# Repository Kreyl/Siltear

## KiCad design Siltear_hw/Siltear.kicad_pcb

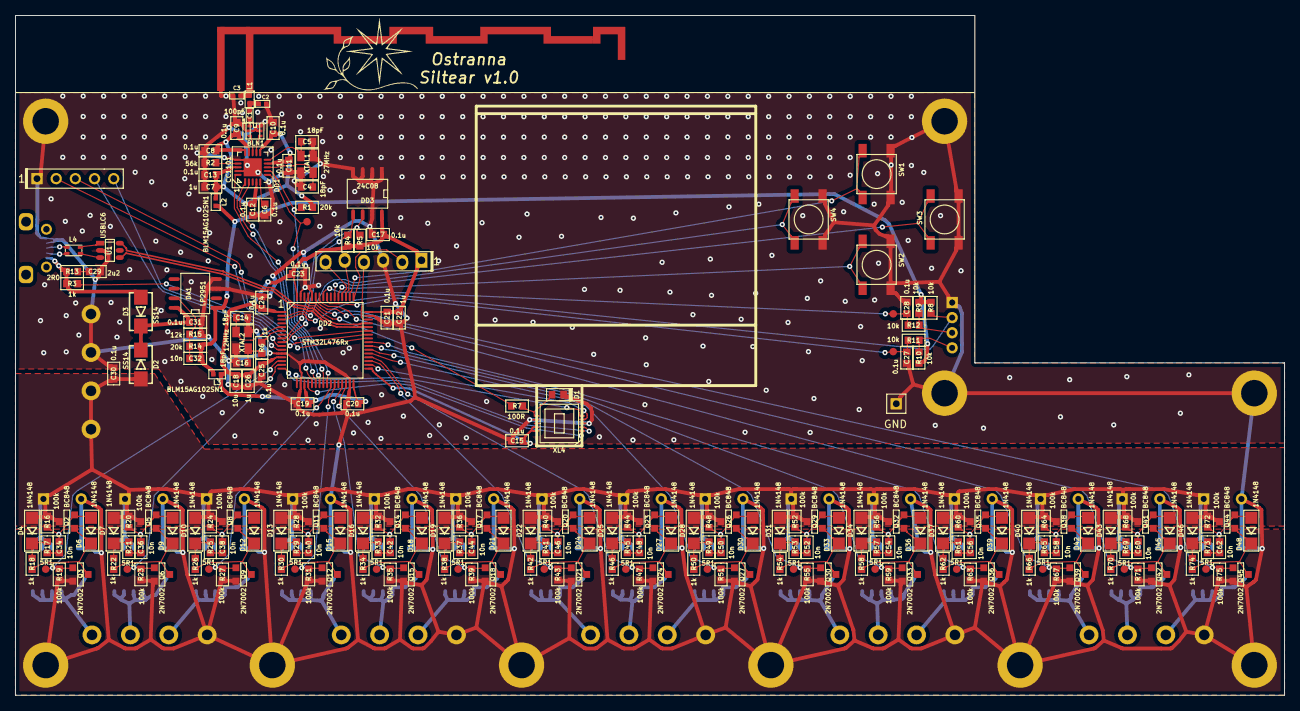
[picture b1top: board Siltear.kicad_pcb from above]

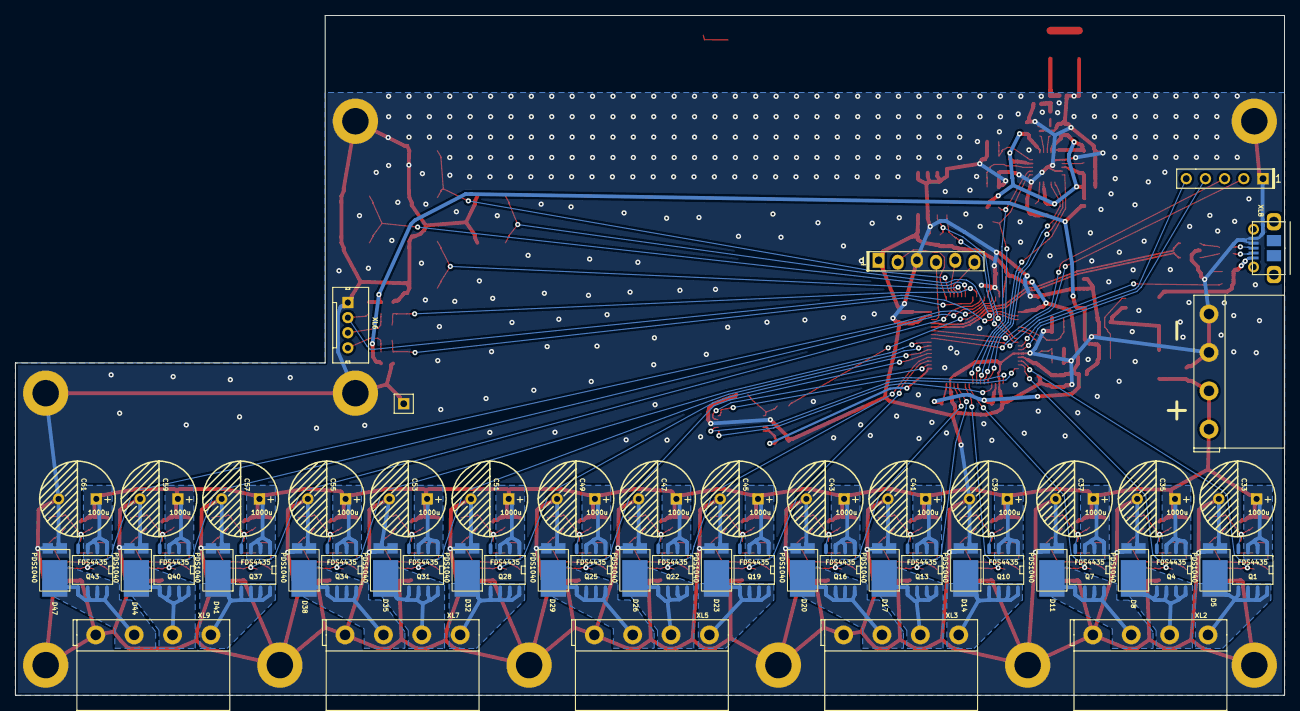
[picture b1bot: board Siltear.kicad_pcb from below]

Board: 4 copper layers, 168.0 x 90.0 mm, 288 parts (53 on the bottom side), 149 nets.

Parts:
ANT1: ANT_GENERAL; ANT_868_IFA_SIMPLEJOY
BLN1: BALUN868JOHANSON; BALUN_JOHANSON868
C1: 100pF; CAP_0402
C2, C3: ***; CAP_0402
C4, C5, C14, C16: 18pF; CAP_0603_Silks
C6, C8, C9, C10, C11, C12, C13, C15, C17, C19, C20, C21, C23, C24, C25, C27, C28, C30, C31: 0.1u; CAP_0603_Silks
C7, C22, C26: 1u; CAP_0603_Silks
C18: 10u; CAP_0603_Silks
C29: 2u2; CAP_0603_Silks
C32, C34, C36, C38, C40, C42, C44, C46, C48, C50, C52, C54, C56, C58, C60, C62: 10n; CAP_0603_Silks
C33, C35, C37, C39, C41, C43, C45, C47, C49, C51, C53, C55, C57, C59, C61: 1000u; CAP_10xxR
D1: LED; LED_0603
D2, D3: SS14; SMA_DO214AC
D4, D6, D7, D9, D10, D12, D13, D15, D16, D18, D19, D21, D22, D24, D25, D27, D28, D30, D31, D33, D34, D36, D37, D39, D40, D42, D43, D45, D46, D48: 1N4148; SOD80C
D5, D8, D11, D14, D17, D20, D23, D26, D29, D32, D35, D38, D41, D44, D47: PDS1040; PowerDI5
DA1: LP2951; SO8_150MIL
DD1: CC1101; QFN20
DD2: STM32L476Rx; LQFP64
DD3: 24C08; SO8_150MIL
HOLE1, HOLE2, HOLE3, HOLE4, HOLE5, HOLE6, HOLE7, HOLE8, HOLE9, HOLE10: HOLE_METALLED; Hole3_5_out6mm
L1: ***; IND_0402
L2, L3: BLM15AG102SN1; IND_0402
L4: 90R; DLW21SN
Logo1: Logo; Ostranna_12d7_10d1
Q1, Q4, Q7, Q10, Q13, Q16, Q19, Q22, Q25, Q28, Q31, Q34, Q37, Q40, Q43: FDS4435; SO8_150MIL
Q2, Q5, Q8, Q11, Q14, Q17, Q20, Q23, Q26, Q29, Q32, Q35, Q38, Q41, Q44: BC848; SOT23-3
Q3, Q6, Q9, Q12, Q15, Q18, Q21, Q24, Q27, Q30, Q33, Q36, Q39, Q42, Q45: 2N7002; SOT23-3
R1, R14: 20k; RES_0603
R2: 56k; RES_0603
R3, R6, R18, R22, R26, R30, R34, R38, R42, R46, R50, R54, R58, R62, R66, R70, R74: 1k; RES_0603
R4, R5, R8, R9, R10, R11, R12: 10k; RES_0603
R7: 100R; RES_0603
R13: 2R0; RES_0603
R15: 12k; RES_0603
R16, R19, R20, R23, R24, R27, R28, R31, R32, R35, R36, R39, R40, R43, R44, R47, R48, R51, R52, R55, R56, R59, R60, R63, R64, R67, R68, R71, R72, R75: 100k; RES_0603
R17, R21, R25, R29, R33, R37, R41, R45, R49, R53, R57, R61, R65, R69, R73: 5R1; RES_0603
SW1, SW2, SW3, SW4: BUTTON; BTN_4x4_SMD
TP1, TP2, TP3, TP4, TP5, TP6, TP7, TP8, TP9, TP10, TP11, TP12, TP13, TP14, TP15, TP16, TP17, TP18: TESTPOINT; TESTPOINT_1MM
U1: USBLC6; SOT23-6
XL1: CONN_6; PLS-6_LOCK
XL2, XL3, XL5, XL7, XL9, XL10: CONN_4; TermiBlockHeader_508_x4_R
XL4: CONN_NOKIA_LCD; NOKIA_10PIN
XL6: CONN_4; WB-04(MW-4M)
XL8: USB_MICRO; USBmicro_MOLEX_1050170001
XL11: CONN_1; PLS-1Square
XL12: CONN_5; PLS-5
XTAL1: 27MHz; 03225C4
XTAL2: 12MHz; 03225C4

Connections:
+3v3: C32.1, DA1.1 (Out), L2.2, L3.2, R8.1, R9.1, R10.1, R14.1
+12v: C30.1, C33.1, C35.1, C37.1, C39.1, C41.1, C43.1, C45.1, C47.1, C49.1, C51.1, C53.1, C55.1, C57.1, C59.1, C61.1, D2.A, D4.A, D7.A, D10.A, D13.A, D16.A, D19.A, D22.A, D25.A, D28.A, D31.A, D34.A, D37.A, D40.A, D43.A, D46.A, Q1.1 (S), Q1.2 (S), Q1.3 (S), Q2.3 (C), Q4.1 (S), Q4.2 (S), Q4.3 (S), Q5.3 (C), Q7.1 (S), Q7.2 (S), Q7.3 (S), Q8.3 (C), Q10.1 (S), Q10.2 (S), Q10.3 (S), Q11.3 (C), Q13.1 (S), Q13.2 (S), Q13.3 (S), Q14.3 (C), Q16.1 (S), Q16.2 (S), Q16.3 (S), Q17.3 (C), Q19.1 (S), Q19.2 (S), Q19.3 (S), Q20.3 (C), Q22.1 (S), Q22.2 (S), Q22.3 (S), Q23.3 (C), Q25.1 (S), Q25.2 (S), Q25.3 (S), Q26.3 (C), Q28.1 (S), Q28.2 (S), Q28.3 (S), Q29.3 (C), Q31.1 (S), Q31.2 (S), Q31.3 (S), Q32.3 (C), Q34.1 (S), Q34.2 (S), Q34.3 (S), Q35.3 (C), Q37.1 (S), Q37.2 (S), Q37.3 (S), Q38.3 (C), Q40.1 (S), Q40.2 (S), Q40.3 (S), Q41.3 (C), Q43.1 (S), Q43.2 (S), Q43.3 (S), Q44.3 (C), R16.1, R20.1, R24.1, R28.1, R32.1, R36.1, R40.1, R44.1, R48.1, R52.1, R56.1, R60.1, R64.1, R68.1, R72.1, XL10.1, XL10.2 (PM)
+PwrMCU: C17.2, C18.2, C19.2, C20.2, C21.2, C22.2, C23.2, C24.2, C25.2, C26.2, DD2.1 (VBAT), DD2.13 (VDDA/VREF+), DD2.19 (VDD), DD2.32 (VDD), DD2.48 (VDDUSB), DD2.64 (VDD), DD3.8 (Vcc), L3.1, R4.1, R5.2, XL1.1
/5V_USB: D3.A, R3.2, R13.1, XL8.1 (UVcc)
/+PWRIN: C31.1, D2.C, D3.C, DA1.8 (In)
/ANT1: C1.1, C2.1, L1.2
/ANT2: ANT1.1 (RF), C3.1, L1.1
/B1: D11.C, Q7.5 (D), Q7.6 (D), Q7.7 (D), Q7.8 (D), XL2.2 (PM)
/B2: D20.C, Q16.5 (D), Q16.6 (D), Q16.7 (D), Q16.8 (D), XL3.2 (PM)
/B3: D29.C, Q25.5 (D), Q25.6 (D), Q25.7 (D), Q25.8 (D), XL5.2 (PM)
/B4: D38.C, Q34.5 (D), Q34.6 (D), Q34.7 (D), Q34.8 (D), XL7.2 (PM)
/B5: D47.C, Q43.5 (D), Q43.6 (D), Q43.7 (D), Q43.8 (D), XL9.2 (PM)
/BTN1: DD2.50 (T2C1/PA15), SW1.1
/BTN2: DD2.53 (MOSI3/TX5/CK3/SDIO_CK/PC12), SW2.1
/BTN3: DD2.54 (RX5/SDIO_CMD/PD2), SW3.1
/BTN4: DD2.2 (WKUP2/RTC_OUT/PC13), SW4.1
/BTN5: DD2.3 (OC32IN/PC14), R8.2, XL6.2 (PM)
/CC_CS: DD1.7 (CSn), DD2.25 (ADC12-14/RX3/PC5), R1.1
/CC_GDO0: DD1.6 (GDO0), DD2.24 (ADC12-13/TX3/PC4), TP1.1
/CC_MISO: DD1.2 (SO(GDO1)), DD2.22 (ADC12-11/T3C1/T16C1/QSPI3/MISO1/PA6)
/CC_MOSI: DD1.20 (SI), DD2.23 (ADC12-12/T3C2/T17C1/QSPI2/MOSI1/PA7)
/CC_SCK: DD1.1 (SCLK), DD2.21 (ADC12-10/T2C1/DAC2/SCK1/PA5)
/D+: DD2.45 (OTG_DP/PA12), U1.6 (I/O1)
/D-: DD2.44 (OTG_DM/T1C4/PA11), U1.4 (I/O2)
/DIN2+: L4.2, U1.1 (I/O1)
/DIN2-: L4.3, U1.3 (I/O2)
/DIN+: L4.1, XL8.3 (D+)
/DIN-: L4.4, XL8.2 (D-)
/ENCODER1: C27.2, DD2.56 (PB4/MISO1/MISO3/T3C1), R11.2, TP2.1
/ENCODER2: C28.2, DD2.57 (PB5/MOSI1/MOSI3/T3C2/CK1/LPTIM1_IN1), R12.2, TP3.1
/G1: D8.C, Q4.5 (D), Q4.6 (D), Q4.7 (D), Q4.8 (D), XL2.3
/G2: D17.C, Q13.5 (D), Q13.6 (D), Q13.7 (D), Q13.8 (D), XL3.3
/G3: D26.C, Q22.5 (D), Q22.6 (D), Q22.7 (D), Q22.8 (D), XL5.3
/G4: D35.C, Q31.5 (D), Q31.6 (D), Q31.7 (D), Q31.8 (D), XL7.3
/G5: D44.C, Q40.5 (D), Q40.6 (D), Q40.7 (D), Q40.8 (D), XL9.3
/LCD_PWR: C15.1, DD2.33 (PB12/CK3), XL4.9 (VDD), XL4.10 (VDDI)
/LCD_SCLK: DD2.20 (ADC12-9/LPTIM2_OUT/DAC1/CK2/PA4), XL4.1 (CLK)
/LCD_SDA: DD2.16 (ADC12-7/WKUP4/T15C1/T2C3/T5C3/TX2/PA2), XL4.2 (DATA)
/LCD_XCS: DD2.34 (PB13/SCK2/SCL2), XL4.4 (CS)
/LCD_XRES: DD2.17 (ADC12-8/T15C2/T2C4/T5C4/RX2/PA3), XL4.5 (RST)
/PA8: DD2.41 (OTG_SOF/LPTIM2_OUT/MCO/T1C1/CK1/PA8), XL12.2
/PA10: DD2.43 (OTG_ID/T1C3/RX1/PA10), XL12.3
/PC2: DD2.10 (ADC123-3/LPTIM1_IN2/MISO2/PC2), XL12.5
/PC3: DD2.11 (ADC123-4/MOSI2/PC3), XL12.4
/PWM01: DD2.14 (ADC12-5/WKUP1/T2C1/T5C1/TX4/PA0), Q3.1 (G), R19.1, TP4.1
/PWM02: DD2.15 (ADC12-6/T2C2/T5C2/RX4/PA1), Q6.1 (G), R23.1, TP5.1
/PWM03: DD2.26 (PB0/T3C3/QSPI1/ADC12-15), Q9.1 (G), R27.1, TP6.1
/PWM04: DD2.27 (PB1/T3C4/QSPI0/LPTIM2_IN1/ADC12-16), Q12.1 (G), R31.1, TP7.1
/PWM05: DD2.29 (PB10/T2C3/SCK2/SCL2/TX3/LPRX1/QSPI_CLK), Q15.1 (G), R35.1, TP8.1
/PWM06: DD2.30 (PB11/T2C4/SDA2/RX3/LPTX1/QSPI_NCS), Q18.1 (G), R39.1, TP9.1
/PWM07: DD2.35 (PB14/MISO2/SDA2/T15C1), Q21.1 (G), R43.1, TP10.1
/PWM08: DD2.36 (PB15/MOSI2/T15C2), Q24.1 (G), R47.1, TP11.1
/PWM09: DD2.37 (T3C1/T8C1/SDIO_D6/PC6), Q27.1 (G), R51.1, TP12.1
/PWM10: DD2.38 (T3C2/T8C2/SDIO_D7/PC7), Q30.1 (G), R55.1, TP13.1
/PWM11: DD2.39 (T3C3/T8C3/SDIO_D0/PC8), Q33.1 (G), R59.1, TP14.1
/PWM12: DD2.40 (OTG_NOE/T3C4/T8C4/SDIO_D1/PC9), Q36.1 (G), R63.1, TP15.1
/PWM13: DD2.58 (PB6/SCL1/T4C1/TX1), Q39.1 (G), R67.1, TP16.1
/PWM14: DD2.59 (PB7/SDA1/T4C2/RX1/LPTIM1_IN2), Q42.1 (G), R71.1, TP17.1
/PWM15: DD2.61 (PB8/SDIO_D4/T4C3/T16C1/SCL1), Q45.1 (G), R75.1, TP18.1
/PWM16: DD2.62 (PB9/SDIO_D5/T4C4/T17C1/SDA1/IR_OUT), R7.1
/R1: D5.C, Q1.5 (D), Q1.6 (D), Q1.7 (D), Q1.8 (D), XL2.4
/R2: D14.C, Q10.5 (D), Q10.6 (D), Q10.7 (D), Q10.8 (D), XL3.4
/R3: D23.C, Q19.5 (D), Q19.6 (D), Q19.7 (D), Q19.8 (D), XL5.4
/R4: D32.C, Q28.5 (D), Q28.6 (D), Q28.7 (D), Q28.8 (D), XL7.4
/R5: D41.C, Q37.5 (D), Q37.6 (D), Q37.7 (D), Q37.8 (D), XL9.4
/RF1: BLN1.4 (Bal2), DD1.12 (RF_P)
/RF2: BLN1.3 (Bal1), DD1.13 (RF_N)
/SCL_EE: DD2.8 (ADC123-1/LPTIM1_2_IN1/SCL3/LPRX1/PC0), DD3.6 (SCL), R5.1
/SDA_EE: DD2.9 (ADC123-2/LPTIM1_OUT/SDA3/LPTX1/PC1), DD3.5 (SDA), R4.2
/SWCLK: DD2.49 (SWCLK/PA14), XL1.2
/SWDIO: DD2.46 (SWDIO/PA13), XL1.4
/UART_RX: DD2.52 (MISO3/RX4/RX3/SDIO_D3/PC11), XL1.6
/UART_TX: DD2.51 (SCK3/TX4/TX3/SDIO_D2/PC10), XL1.5
GND: ANT1.2 (GND), BLN1.2 (GND), BLN1.5 (GND), BLN1.6 (GND), C2.2, C3.2, C4.2, C5.2, C6.1, C7.2, C8.2, C9.2, C10.2, C11.2, C12.2, C13.2, C14.2, C15.2, C16.2, C17.1, C18.1, C19.1, C20.1, C21.1, C22.1, C23.1, C24.1, C25.1, C26.1, C27.1, C28.1, C29.2, C30.2, C31.2, C33.2, C35.2, C37.2, C39.2, C41.2, C43.2, C45.2, C47.2, C49.2, C51.2, C53.2, C55.2, C57.2, C59.2, C61.2, D1.C, D5.A, D8.A, D11.A, D14.A, D17.A, D20.A, D23.A, D26.A, D29.A, D32.A, D35.A, D38.A, D41.A, D44.A, D47.A, DA1.3 (Shdn), DA1.4 (GND), DD1.16 (GND), DD1.19 (GND), DD1.PAD (GND), DD2.12 (VSSA/VREF-), DD2.18 (VSS), DD2.31 (VSS), DD2.47 (VSS), DD2.60 (BOOT0), DD2.63 (VSS), DD3.1 (A0), DD3.2 (A1), DD3.3 (A2), DD3.4 (GND), DD3.7 (WP), HOLE1.H, HOLE2.H, HOLE3.H, HOLE4.H, HOLE5.H, HOLE6.H, HOLE7.H, HOLE8.H, HOLE9.H, HOLE10.H, Q3.2 (S), Q6.2 (S), Q9.2 (S), Q12.2 (S), Q15.2 (S), Q18.2 (S), Q21.2 (S), Q24.2 (S), Q27.2 (S), Q30.2 (S), Q33.2 (S), Q36.2 (S), Q39.2 (S), Q42.2 (S), Q45.2 (S), R2.2, R15.2, R19.2, R23.2, R27.2, R31.2, R35.2, R39.2, R43.2, R47.2, R51.2, R55.2, R59.2, R63.2, R67.2, R71.2, R75.2, SW1.2, SW2.2, SW3.2, SW4.2, U1.2 (GND), XL1.3, XL2.1, XL3.1, XL4.3 (GND), XL4.7 (LED-), XL5.1, XL6.1, XL7.1, XL8.4 (UID), XL8.5 (UGND), XL9.1, XL10.3, XL10.4, XL11.1, XL12.1, XTAL1.H, XTAL2.H
unnamed: BLN1.1 (Unbal), C1.2
unnamed: C4.1, DD1.8 (XOSC_Q1), XTAL1.1
unnamed: C5.1, DD1.10 (XOSC_Q2), XTAL1.2
unnamed: C6.2, DD1.5 (DCOUPL)
unnamed: C14.1, DD2.5 (PH0/OSCIN), XTAL2.1
unnamed: C16.1, R6.1, XTAL2.2
unnamed: C29.1, R13.2
unnamed: C32.2, DA1.7 (Feedback), R14.2, R15.1
unnamed: C34.1, D6.A, Q1.4 (G), Q2.2 (E), R16.2
unnamed: C34.2, R17.2
unnamed: C36.1, D9.A, Q4.4 (G), Q5.2 (E), R20.2
unnamed: C36.2, R21.2
unnamed: C38.1, D12.A, Q7.4 (G), Q8.2 (E), R24.2
unnamed: C38.2, R25.2
unnamed: C40.1, D15.A, Q10.4 (G), Q11.2 (E), R28.2
unnamed: C40.2, R29.2
unnamed: C42.1, D18.A, Q13.4 (G), Q14.2 (E), R32.2
unnamed: C42.2, R33.2
unnamed: C44.1, D21.A, Q16.4 (G), Q17.2 (E), R36.2
unnamed: C44.2, R37.2
unnamed: C46.1, D24.A, Q19.4 (G), Q20.2 (E), R40.2
unnamed: C46.2, R41.2
unnamed: C48.1, D27.A, Q22.4 (G), Q23.2 (E), R44.2
unnamed: C48.2, R45.2
unnamed: C50.1, D30.A, Q25.4 (G), Q26.2 (E), R48.2
unnamed: C50.2, R49.2
unnamed: C52.1, D33.A, Q28.4 (G), Q29.2 (E), R52.2
unnamed: C52.2, R53.2
unnamed: C54.1, D36.A, Q31.4 (G), Q32.2 (E), R56.2
unnamed: C54.2, R57.2
unnamed: C56.1, D39.A, Q34.4 (G), Q35.2 (E), R60.2
unnamed: C56.2, R61.2
unnamed: C58.1, D42.A, Q37.4 (G), Q38.2 (E), R64.2
unnamed: C58.2, R65.2
unnamed: C60.1, D45.A, Q40.4 (G), Q41.2 (E), R68.2
unnamed: C60.2, R69.2
unnamed: C62.1, D48.A, Q43.4 (G), Q44.2 (E), R72.2
unnamed: C62.2, R73.2
unnamed: D1.A, R7.2, XL4.6 (LED+)
unnamed: D4.C, R17.1, R18.2
unnamed: D6.C, Q2.1 (B), Q3.3 (D), R18.1
unnamed: D7.C, R21.1, R22.2
unnamed: D9.C, Q5.1 (B), Q6.3 (D), R22.1
unnamed: D10.C, R25.1, R26.2
unnamed: D12.C, Q8.1 (B), Q9.3 (D), R26.1
unnamed: D13.C, R29.1, R30.2
unnamed: D15.C, Q11.1 (B), Q12.3 (D), R30.1
unnamed: D16.C, R33.1, R34.2
unnamed: D18.C, Q14.1 (B), Q15.3 (D), R34.1
unnamed: D19.C, R37.1, R38.2
unnamed: D21.C, Q17.1 (B), Q18.3 (D), R38.1
unnamed: D22.C, R41.1, R42.2
unnamed: D24.C, Q20.1 (B), Q21.3 (D), R42.1
unnamed: D25.C, R45.1, R46.2
unnamed: D27.C, Q23.1 (B), Q24.3 (D), R46.1
unnamed: D28.C, R49.1, R50.2
unnamed: D30.C, Q26.1 (B), Q27.3 (D), R50.1
unnamed: D31.C, R53.1, R54.2
unnamed: D33.C, Q29.1 (B), Q30.3 (D), R54.1
unnamed: D34.C, R57.1, R58.2
unnamed: D36.C, Q32.1 (B), Q33.3 (D), R58.1
unnamed: D37.C, R61.1, R62.2
unnamed: D39.C, Q35.1 (B), Q36.3 (D), R62.1
unnamed: D40.C, R65.1, R66.2
unnamed: D42.C, Q38.1 (B), Q39.3 (D), R66.1
unnamed: D43.C, R69.1, R70.2
unnamed: D45.C, Q41.1 (B), Q42.3 (D), R70.1
unnamed: D46.C, R73.1, R74.2
unnamed: D48.C, Q44.1 (B), Q45.3 (D), R74.1
unnamed: DD1.17 (RBIAS), R2.1
unnamed: DD2.6 (PH1/OSCOUT), R6.2
unnamed: DD2.42 (OTG_VBUS/T1C2/TX1/PA9), R3.1
unnamed: R10.2, R11.1, XL6.4
unnamed: R9.2, R12.1, XL6.3
VCC: C7.1, C8.1, C9.1, C10.1, C11.1, C12.1, C13.1, DD1.4 (DVDD), DD1.9 (AVDD), DD1.11 (AVDD), DD1.14 (AVDD), DD1.15 (AVDD), DD1.18 (DGUARD), L2.1, R1.2

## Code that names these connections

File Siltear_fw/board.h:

/*
 * board.h
 *
 *  Created on: 05 08 2018
 *      Author: Kreyl
 */

#pragma once

// ==== General ====
#define APP_NAME            "Dragon"

// Version of PCB
#define PCB_VER                 1

// MCU type as defined in the ST header.
#define STM32L476xx

// Freq of external crystal if any. Leave it here even if not used.
#define CRYSTAL_FREQ_HZ         12000000

// OS timer settings
#define STM32_ST_IRQ_PRIORITY   2
#define STM32_ST_USE_TIMER      5
#define SYS_TIM_CLK             (Clk.APB1FreqHz)    // Timer 5 is clocked by APB1

//  Periphery
#define I2C1_ENABLED            FALSE
#define I2C2_ENABLED            FALSE
#define I2C3_ENABLED            TRUE

#define ADC_REQUIRED            FALSE
#define STM32_DMA_REQUIRED      TRUE    // Leave this macro name for OS

#if 1 // ========================== GPIO =======================================
// EXTI
#define INDIVIDUAL_EXTI_IRQ_REQUIRED    FALSE

// PWM
#define PWM01_PIN       { GPIOA,  0,  TIM2, 1, invNotInverted, omPushPull, 255 }
#define PWM02_PIN       { GPIOA,  1,  TIM2, 2, invNotInverted, omPushPull, 255 }
#define PWM03_PIN       { GPIOB,  0,  TIM3, 3, invNotInverted, omPushPull, 255 }
#define PWM04_PIN       { GPIOB,  1,  TIM3, 4, invNotInverted, omPushPull, 255 }
#define PWM05_PIN       { GPIOB, 10,  TIM2, 3, invNotInverted, omPushPull, 255 }
#define PWM06_PIN       { GPIOB, 11,  TIM2, 4, invNotInverted, omPushPull, 255 }
#define PWM07_PIN       { GPIOB, 14, TIM15, 1, invNotInverted, omPushPull, 255 }
#define PWM08_PIN       { GPIOB, 15, TIM15, 2, invNotInverted, omPushPull, 255 }
#define PWM09_PIN       { GPIOC,  6,  TIM8, 1, invNotInverted, omPushPull, 255 }
#define PWM10_PIN       { GPIOC,  7,  TIM8, 2, invNotInverted, omPushPull, 255 }
#define PWM11_PIN       { GPIOC,  8,  TIM8, 3, invNotInverted, omPushPull, 255 }
#define PWM12_PIN       { GPIOC,  9,  TIM8, 4, invNotInverted, omPushPull, 255 }
#define PWM13_PIN       { GPIOB,  6,  TIM4, 1, invNotInverted, omPushPull, 255 }
#define PWM14_PIN       { GPIOB,  7,  TIM4, 2, invNotInverted, omPushPull, 255 }
#define PWM15_PIN       { GPIOB,  8,  TIM4, 3, invNotInverted, omPushPull, 255 }
#define PWM16_PIN       { GPIOB,  9,  TIM4, 4, invNotInverted, omPushPull, 255 }

// LCD
#define LCD_SDA         GPIOA, 2 // USART2
#define LCD_XRES        GPIOA, 3
#define LCD_SCLK        GPIOA, 4
#define LCD_AF          AF7
#define LCD_XCS         GPIOB, 13
#define LCD_BCKLT       PWM16_PIN
#define LCD_PWR         GPIOB, 12

// Radio: SPI, PGpio, Sck, Miso, Mosi, Cs, Gdo0
#define CC_Setup0       SPI1, GPIOA, 5,6,7, GPIOC,5, GPIOC,4

// Just pins
#define GPIO_PA8        GPIOA, 8
#define GPIO_PA10       GPIOA, 10
#define GPIO_PC2        GPIOC, 2
#define GPIO_PC3        GPIOC, 3

// Buttons
#define BTN1_PIN        GPIOA, 15, pudPullUp
#define BTN2_PIN        GPIOC, 12, pudPullUp
#define BTN3_PIN        GPIOD,  2, pudPullUp
#define BTN4_PIN        GPIOC, 13, pudPullUp
#define BTN5_PIN        GPIOC, 14, pudPullUp

// Encoder
#define ENC1_PIN        GPIOB, 4, pudPullUp
#define ENC2_PIN        GPIOB, 5, pudPullUp

// UART
#define UART_GPIO       GPIOC
#define UART_TX_PIN     10
#define UART_RX_PIN     11

// I2C
//#define I2C1_GPIO       GPIOB
//#define I2C1_SCL        6
//#define I2C1_SDA        7
//#define I2C2_GPIO       GPIOB
//#define I2C2_SCL        10
//#define I2C2_SDA        11
#define I2C3_GPIO       GPIOC
#define I2C3_SCL        0
#define I2C3_SDA        1
// I2C Alternate Function
#define I2C_AF          AF4

// USB
#define USB_DM          GPIOA, 11
#define USB_DP          GPIOA, 12
#define USB_AF          AF10
// USB detect
#define USB_DETECT_PIN  GPIOA, 9

#endif // GPIO

#if 1 // =========================== I2C =======================================
// i2cclkPCLK1, i2cclkSYSCLK, i2cclkHSI
#define I2C_CLK_SRC     i2cclkHSI
#define I2C_BAUDRATE_HZ 400000
#endif

#if ADC_REQUIRED // ======================= Inner ADC ==========================
// Clock divider: clock is generated from the APB2
#define ADC_CLK_DIVIDER		adcDiv2

// ADC channels
#define ADC_BATTERY_CHNL 	14
// ADC_VREFINT_CHNL
#define ADC_CHANNELS        { ADC_BATTERY_CHNL, ADC_VREFINT_CHNL }
#define ADC_CHANNEL_CNT     2   // Do not use countof(AdcChannels) as preprocessor does not know what is countof => cannot check
#define ADC_SAMPLE_TIME     ast24d5Cycles
#define ADC_OVERSAMPLING_RATIO  64   // 1 (no oversampling), 2, 4, 8, 16, 32, 64, 128, 256
#endif

#if 1 // =========================== DMA =======================================
// ==== Uart ====
// Remap is made automatically if required
#define UART_DMA_TX     STM32_DMA_STREAM_ID(2, 3)
#define UART_DMA_RX     STM32_DMA_STREAM_ID(2, 5)
#define UART_DMA_CHNL   2
#define UART_DMA_TX_MODE(Chnl) (STM32_DMA_CR_CHSEL(Chnl) | DMA_PRIORITY_LOW | STM32_DMA_CR_MSIZE_BYTE | STM32_DMA_CR_PSIZE_BYTE | STM32_DMA_CR_MINC | STM32_DMA_CR_DIR_M2P | STM32_DMA_CR_TCIE)
#define UART_DMA_RX_MODE(Chnl) (STM32_DMA_CR_CHSEL(Chnl) | DMA_PRIORITY_MEDIUM | STM32_DMA_CR_MSIZE_BYTE | STM32_DMA_CR_PSIZE_BYTE | STM32_DMA_CR_MINC | STM32_DMA_CR_DIR_P2M | STM32_DMA_CR_CIRC)

// LCD
#define UARTLCD_DMA_TX          STM32_DMA_STREAM_ID(1, 7)
#define UARTLCD_DMA_CHNL        2
#define UARTLCD_DMA_MODE(Chnl)  (STM32_DMA_CR_CHSEL(Chnl) | DMA_PRIORITY_LOW | STM32_DMA_CR_MSIZE_BYTE | STM32_DMA_CR_PSIZE_BYTE | STM32_DMA_CR_MINC | STM32_DMA_CR_DIR_M2P | STM32_DMA_CR_TCIE)

// ==== I2C ====
#define I2C_USE_DMA     TRUE
//#define I2C1_DMA_TX     STM32_DMA_STREAM_ID(1, 6)
//#define I2C1_DMA_RX     STM32_DMA_STREAM_ID(1, 7)
//#define I2C1_DMA_CHNL   3
//#define I2C2_DMA_TX     STM32_DMA_STREAM_ID(1, 4)
//#define I2C2_DMA_RX     STM32_DMA_STREAM_ID(1, 5)
//#define I2C2_DMA_CHNL   3
#define I2C3_DMA_TX     STM32_DMA_STREAM_ID(1, 2)
#define I2C3_DMA_RX     STM32_DMA_STREAM_ID(1, 3)
#define I2C3_DMA_CHNL   3

#if ADC_REQUIRED
#define ADC_DMA         STM32_DMA1_STREAM1
#define ADC_DMA_MODE    STM32_DMA_CR_CHSEL(0) |   /* DMA1 Stream1 Channel0 */ \
                        DMA_PRIORITY_LOW | \
                        STM32_DMA_CR_MSIZE_HWORD | \
                        STM32_DMA_CR_PSIZE_HWORD | \
                        STM32_DMA_CR_MINC |       /* Memory pointer increase */ \
                        STM32_DMA_CR_DIR_P2M |    /* Direction is peripheral to memory */ \
                        STM32_DMA_CR_TCIE         /* Enable Transmission Complete IRQ */
#endif // ADC

#endif // DMA

#if 1 // ========================== USART ======================================
#define PRINTF_FLOAT_EN FALSE
#define UART_TXBUF_SZ   4096
#define UART_RXBUF_SZ   99
#define CMD_BUF_SZ      256

#define CMD_UART        UART4

#define CMD_UART_PARAMS \
    CMD_UART, UART_GPIO, UART_TX_PIN, UART_GPIO, UART_RX_PIN, \
    UART_DMA_TX, UART_DMA_RX, UART_DMA_TX_MODE(UART_DMA_CHNL), UART_DMA_RX_MODE(UART_DMA_CHNL), \
    uartclkHSI // Use independent clock

#endif

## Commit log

2021-08-04 + PCB produces + Code started
2021-08-07 Seems working
2021-08-08 + Chnl now is sent, too RC
